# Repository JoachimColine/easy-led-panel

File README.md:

<!--
*** Thank you : https://github.com/othneildrew/Best-README-Template/blob/master/BLANK_README.md
-->

<!-- PROJECT SHIELDS -->
<!--
*** I'm using markdown "reference style" links for readability.
*** Reference links are enclosed in brackets [ ] instead of parentheses ( ).
*** See the bottom of this document for the declaration of the reference variables
*** for contributors-url, forks-url, etc. This is an optional, concise syntax you may use.
*** https://www.markdownguide.org/basic-syntax/#reference-style-links
-->
[![Contributors][contributors-shield]][contributors-url]
[![Forks][forks-shield]][forks-url]
[![Stargazers][stars-shield]][stars-url]
[![Issues][issues-shield]][issues-url]
[![MIT License][license-shield]][license-url]
[![LinkedIn][linkedin-shield]][linkedin-url]

<!-- PROJECT LOGO -->
<br />
<p align="center">

  <h3 align="center">Easy LED Panel</h3>

  <p align="center">
    Assemble, program and simulate up to 8 LED strips driven by a <a href= "https://www.pjrc.com/store/octo28_adaptor.html">Teensy</a> board
    <br />
    <a href="https://www.youtube.com/watch?v=32DB5OOd8oo&ab_channel=JoachimColine">View Demo</a>
    ·
    <a href="https://github.com/JoachimColine/Octobridge/issues">Report Bug</a>
    ·
    <a href="https://github.com/JoachimColine/Octobridge/issues">Request Feature</a>
  </p>
</p>

<!-- ABOUT THE PROJECT -->
## What is it?

This repository aims to
- provide [guidelines](#how-to-build-your-own-led-panel) for assembling and programming a simple LED panel using LED strips,
- give public access to the [PCB files](/kicad) of a component (the _Octobridge_),
- provide a way to [simulate](#how-to-simulate-your-own-led-panel) your LED panel on your computer, allowing easy tests without hardware,
- suggest some [program snippets](/arduino) that can be directly uploaded to your LED panel. (TBD)

I had the chance to put this project to practice with my <a href= "https://www.touchouss.lol/">improv team</a>. By aligning 8 strips of 150 LEDs and with a little programming, we put on a great show!  :sunglasses:

## How to build your own LED panel
### Caution
- LED strips can be dangerous for the human eye, as they produce very bright light. Be careful. Place a diffusing material in front of the LEDs to attenuate the light.
- LED strips draw a lot of power. Be careful. Incorrect or unsafe wiring can be dangerous.

### Working principle
A Teensy-driven LED panel is made up of 3 main parts:
- Power supply, needed for producing light,
- a microcontroller, needed for controlling the RGB values of each LED,
- WS2811b LED strips aligned on top of one another, needed for creating a 2D grid of LEDs. 

To make the bridge between these parts, and to facilitate cable work, I designed a printed circuit board I called the Octobridge. As shown in the simplified illustration below, the Octobridge receives power and data, and distributes it to the LED strips. 

In practice, the power received comes from a 5V DC power supply, and data comes from a <a href= "https://www.pjrc.com/store/octo28_adaptor.html">Teensy</a> board using two CAT6 Ethernet cables. 
This is shown in the illustration below.

The top four LED strips are powered by the top power input and driven by the top CAT6 Ethernet cable.
The bottom four LED strips are powered by the bottom power input and driven by the bottom CAT6 Ethernet cable.

The data sent to the WS2811b chips consists of a series of digital pulses, with each pulse representing a bit of information. 
The timing and sequence of these pulses encode the color and brightness data for each LED.
Each LED interprets the data intended for it and adjusts its color and brightness accordingly. 

By being individually addressable, the WS2811b LEDs can be programmed with high flexibility. 
Programming is particularly easy under the <a href="https://www.arduino.cc/">Arduino</a> framework as explained in the [LED programming section](#how-to-program-your-own-led-panel).

### List of required components
- A <a href= "https://www.pjrc.com/store/octo28_adaptor.html">Teensy</a> board, mounted on an OctoWS2811 Adaptor,
- two CAT6 Ethernet cables,
- a 5V DC power supply (that can draw up to 40A),
- thick wires for connecting the power supply to the Octobridge (the thicker, the better. Too thin wires will burn or cause incorrect LED colors),  
- WS2811b LED strips,
- an Octobridge (the PCB files can be found [here](/kicad)),
- passive components to be soldered on the Octobridge, that is
    - eight 100ohm resistors,
	- eight 1000µF capacitors (6.3V, 3.5mm lead spacing),
	- two single-port, tab-up (not down!) RJ45 connectors (through-hole, 8P8C, shielded, right-angle),
	- eight S3B-XH-A JST connectors,
	- eight JST XH 2.54mm 3-pin wired connectors.

### Step-by-step assembly
- Make sure you have [all the components needed](#list-of-required-components). They can be ordered from the following suppliers:
	- <a href= "https://www.pjrc.com/store/octo28_adaptor.html">PJRC</a>: for the Teensy board,
	- <a href= "https://jlcpcb.com/">JLCPCB</a>: for the Octobridge (the PCB files can be found [here](/kicad)),	
	- Amazon, Aliexpress, etc.: for the rest.
- Once you have gathered all the components,
	- solder the passive components on the Octobridge (watch out for the polarity of your capacitors!),
	- solder the JST XH 2.54mm 3-pin wired connectors to your LED strips (make sure the pin mapping is respected. Refer to the [wiring circuit](/kicad/octobridge.pdf) or to the image below),

	- turn off the power supply and wire it to the Octobridge (watch out for the right GND and 5V connections, as shown in the image below),

	- connect your LED strips and your Teensy board to the Octobridge.
	
We're all set! 

## How to program your own LED panel
The last part of the project is also the most fun: you get to program your own LED animations :sunglasses:.

- Install and run the <a href="https://www.arduino.cc/">Arduino</a> IDE on your computer,
- from the Arduino main window, go to the _Boards Manager_ and install the <a href="https://www.pjrc.com/teensy/td_download.html">Teensy</a> extension by Paul Stoffregen (as shown in the image below),

### Your first LED animation
- go to _Manage Libraries ..._ under the _Tools_ menu, and install the <a href="https://fastled.io/">FastLED</a> and the <a href="https://www.pjrc.com/teensy/td_libs_OctoWS2811.html">OctoWS2811</a> libraries,
- open your first LED animation file by going to _File_&rarr;_Examples_&rarr;_OctoWS2811_&rarr;_BasicTest_FastLED_.
- in the code, edit the value of `NUM_LEDS` to your total number of LEDs.

Finally, plug your Teensy to your computer, upload the sketch, and power up the Octobridge (after checking the wiring). Congratulations, you just brought life to your LED panel! :rocket:

### Programming custom animations
You can create your own animations using the <a href="https://fastled.io/">FastLED</a> and/or the <a href="https://www.pjrc.com/teensy/td_libs_OctoWS2811.html">OctoWS2811</a> libraries. Possibilities are endless! Have fun :grinning:

## How to simulate your own LED panel
Want to test an idea without wiring up hardware? You have come to the right place! 

I have made available a [Python script](/simulator/simulator.py) that simulates an LED panel. 
The downside of this simulator is that it is not using Arduino, which means you will have to re-write the program if you want to upload it to your <a href="https://www.pjrc.com/store/octo28_adaptor.html">Teensy</a>  board. 
However,
- Python is awesome (change my mind),
- you can test your ideas quickly and easily without hardware, 
- resulting animations can be easily visualized and shared,
- programming simulated animations is very similar to programming in Arduino. In other words, translating the Python program to Arduino is fast. For example, see the how the main loop of the scrolling text animation [written in Python](/simulator/animationScrollingText.py)
```
# Python prototyping
def scrollingTextProgram(leds):
    BLUE  = [0, 0, 255]
    RED   = [255, 0, 0]
    YELLOW = [255, 255, 0]
    PAUSE = 40 # milliseconds
    scrollText(leds, " EASY LED PANEL ", RED, BLUE, PAUSE)
    scrollText(leds, " EASY LED PANEL ", YELLOW, RED, PAUSE)
    scrollText(leds, " EASY LED PANEL ", BLUE, YELLOW, PAUSE)
}
```
compares to the same one [written in Arduino](/arduino/animationScrollingText.ino)
```
/*Arduino implementation*/
void loop() {
  int BLUE   = 0x0000FF;
  int RED    = 0xFF0000;
  int YELLOW = 0xFFFF00;
  int PAUSE  = 40; // milliseconds
  scrollText(" EASY LED PANEL ", 16 /*char array size*/, RED, BLUE, PAUSE);
  scrollText(" EASY LED PANEL ", 16 /*char array size*/, YELLOW, RED, PAUSE);
  scrollText(" EASY LED PANEL ", 16 /*char array size*/, BLUE, YELLOW, PAUSE);
}
```

### Requirements
You will need to install <a href="https://www.python.org/downloads/">Python</a> by downloading and running their latest installer. See <a href="https://github.com/PackeTsar/Install-Python/blob/master/README.md">this repository</a> for a complete tutorial for installing Python on common operating systems.
The simulator depends on <a href="https://www.pygame.org/wiki/GettingStarted">Pygame</a> which you also need to install. This is easily done using the command
```
pip install pygame
```
from the terminal.

### Your first simulation
Once you have installed [all requirements](#requirements), run the [animation example](/simulator/animationExample.py) script with the command
```
python animationExample.py
```
from the terminal. A window will pop, displaying the following LED animation: 

<p align="center">
  
</p>

Congratulations, you just brought life to your simulated LED panel! :rocket:
### Programming custom simulated animations
You can create your own animations using the simulator. I would recommend doing so in a new Python script of your own in the [simulator](/simulator) directory. A great way to start would be to copy the [animation example](/simulator/animationExample.py) and edit it in a new file.

<!-- MARKDOWN LINKS & IMAGES -->
<!-- https://www.markdownguide.org/basic-syntax/#reference-style-links -->
[contributors-shield]: https://img.shields.io/github/contributors/JoachimColine/Octobridge.svg?style=flat-square
[contributors-url]: https://github.com/JoachimColine/Octobridge/graphs/contributors
[forks-shield]: https://img.shields.io/github/forks/JoachimColine/Octobridge.svg?style=flat-square
[forks-url]: https://github.com/JoachimColine/Octobridge/network/members
[stars-shield]: https://img.shields.io/github/stars/JoachimColine/Octobridge.svg?style=flat-square
[stars-url]: https://github.com/JoachimColine/Octobridge/stargazers
[issues-shield]: https://img.shields.io/github/issues/JoachimColine/Octobridge.svg?style=flat-square
[issues-url]: https://github.com/JoachimColine/Octobridge/issues
[license-shield]: https://img.shields.io/github/license/JoachimColine/Octobridge.svg?style=flat-square
[license-url]: https://github.com/JoachimColine/Octobridge/blob/master/LICENSE
[linkedin-shield]: https://img.shields.io/badge/-LinkedIn-black.svg?style=flat-square&logo=linkedin&colorB=555
[linkedin-url]: https://linkedin.com/in/joachim-coline

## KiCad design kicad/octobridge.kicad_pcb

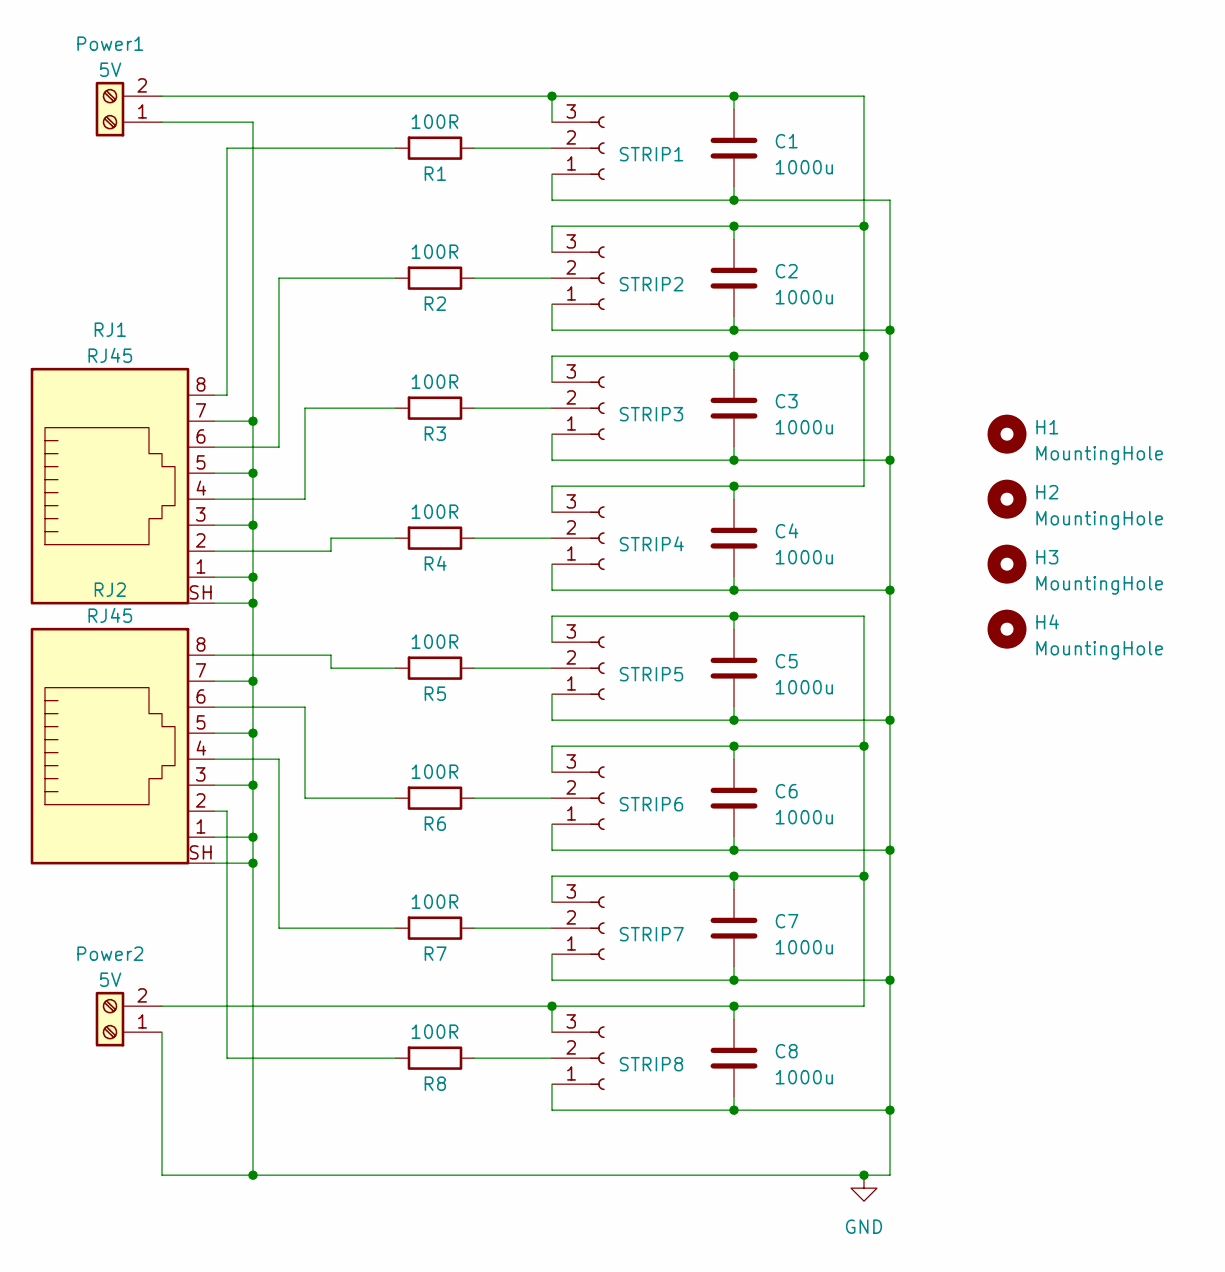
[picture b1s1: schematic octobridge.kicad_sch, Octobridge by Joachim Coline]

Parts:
C1, C2, C3, C4, C5, C6, C7, C8: 1000u; C_Radial_D8.0mm_H11.5mm_P3.50mm
H1, H2, H3, H4: MountingHole; MountingHole_2.5mm
Power1, Power2: 5V; TerminalBlock_Phoenix_PT-1,5-2-5.0-H_1x02_P5.00mm_Horizontal
R1, R2, R3, R4, R5, R6, R7, R8: 100R; R_Axial_DIN0207_L6.3mm_D2.5mm_P10.16mm_Horizontal
RJ1, RJ2: RJ45; RJ45_Amphenol_RJHSE538X
STRIP1, STRIP2, STRIP3, STRIP4, STRIP5, STRIP6, STRIP7, STRIP8: JST_XH_S3B-XH-A_1x03_P2.50mm_Horizontal

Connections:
GND: C1.2, C2.2, C3.2, C4.2, C5.2, C6.2, C7.2, C8.2, Power1.1, Power2.1, RJ1.1, RJ1.3, RJ1.5, RJ1.7, RJ1.SH, RJ2.1, RJ2.3, RJ2.5, RJ2.7, RJ2.SH, STRIP1.1, STRIP2.1, STRIP3.1, STRIP4.1, STRIP5.1, STRIP6.1, STRIP7.1, STRIP8.1
unnamed: C1.1, C2.1, C3.1, C4.1, Power1.2, STRIP1.3, STRIP2.3, STRIP3.3, STRIP4.3
unnamed: C5.1, C6.1, C7.1, C8.1, Power2.2, STRIP5.3, STRIP6.3, STRIP7.3, STRIP8.3
unnamed: R1.2, RJ1.8
unnamed: R2.2, RJ1.6
unnamed: R3.2, RJ1.4
unnamed: R4.2, RJ1.2
unnamed: R5.2, RJ2.8
unnamed: R6.2, RJ2.6
unnamed: R7.2, RJ2.4
unnamed: R8.2, RJ2.2
unnamed: R1.1, STRIP1.2
unnamed: R2.1, STRIP2.2
unnamed: R3.1, STRIP3.2
unnamed: R4.1, STRIP4.2
unnamed: R5.1, STRIP5.2
unnamed: R6.1, STRIP6.2
unnamed: R7.1, STRIP7.2
unnamed: R8.1, STRIP8.2

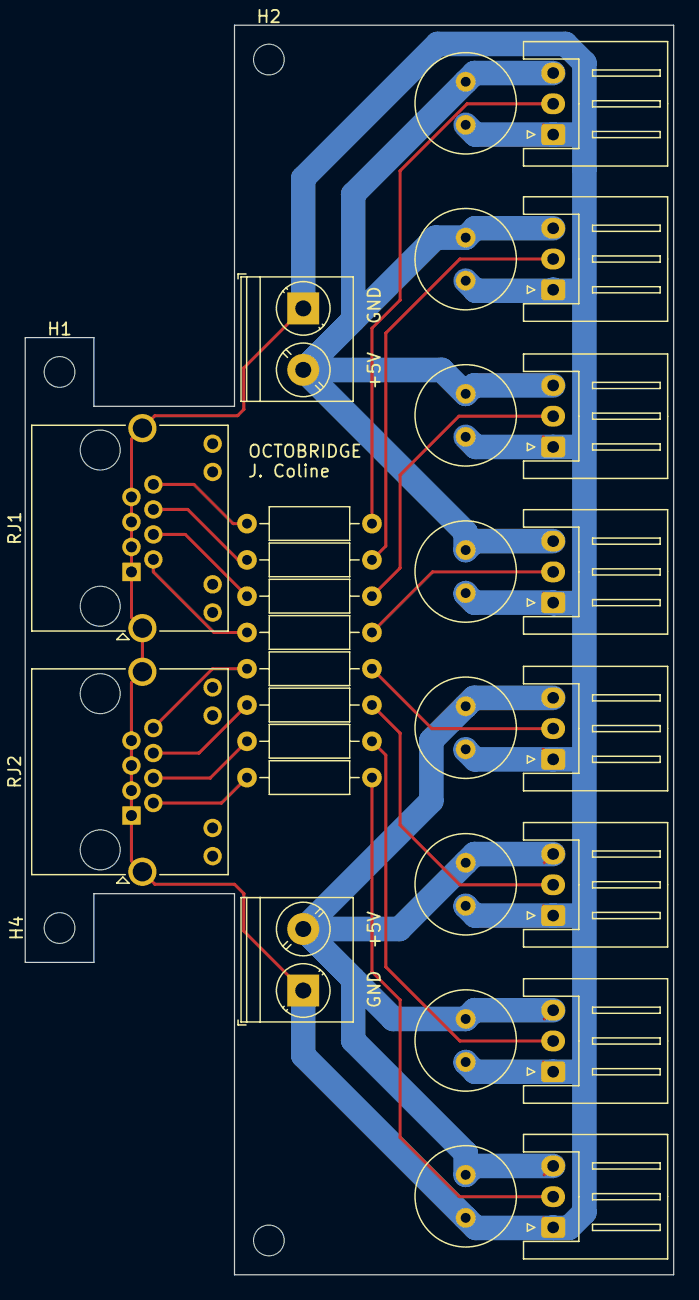
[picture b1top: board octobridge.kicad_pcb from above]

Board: 2 copper layers, 52.7 x 101.6 mm, 32 parts (0 on the bottom side), 19 nets.

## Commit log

2024-04-07 ADD: Octobridge illustration
2024-04-07 ADD: Octobridge kicad files
2024-04-08 ADD: README file
2024-04-21 ADD: README working principle
2024-04-21 ADD: README caution message
2024-04-22 ADD: README required components
2024-04-28 ADD: step-by-step assembly
2024-04-29 ADD: your first LED animation
2024-05-14 CHG: set project name to easy led panel
2024-06-16 ADD: Python LED simulator
2024-06-18 ADD: scrolling text simulation
2024-06-18 ADD: scrolling text arduino implementation
2024-06-18 ADD: real led panel illustration
2024-06-18 ADD: program comparison in readme
2024-06-22 ADD: pip install pygame in readme
2025-01-12 IMP: image generator from simulator
2025-01-12 IMP: Add image converter
    This commit allows to convert a PNG image to an array usable by the
    arduino code.
2025-01-12 IMP: small simulator improvements
2025-05-12 CHG: use .webp image format
